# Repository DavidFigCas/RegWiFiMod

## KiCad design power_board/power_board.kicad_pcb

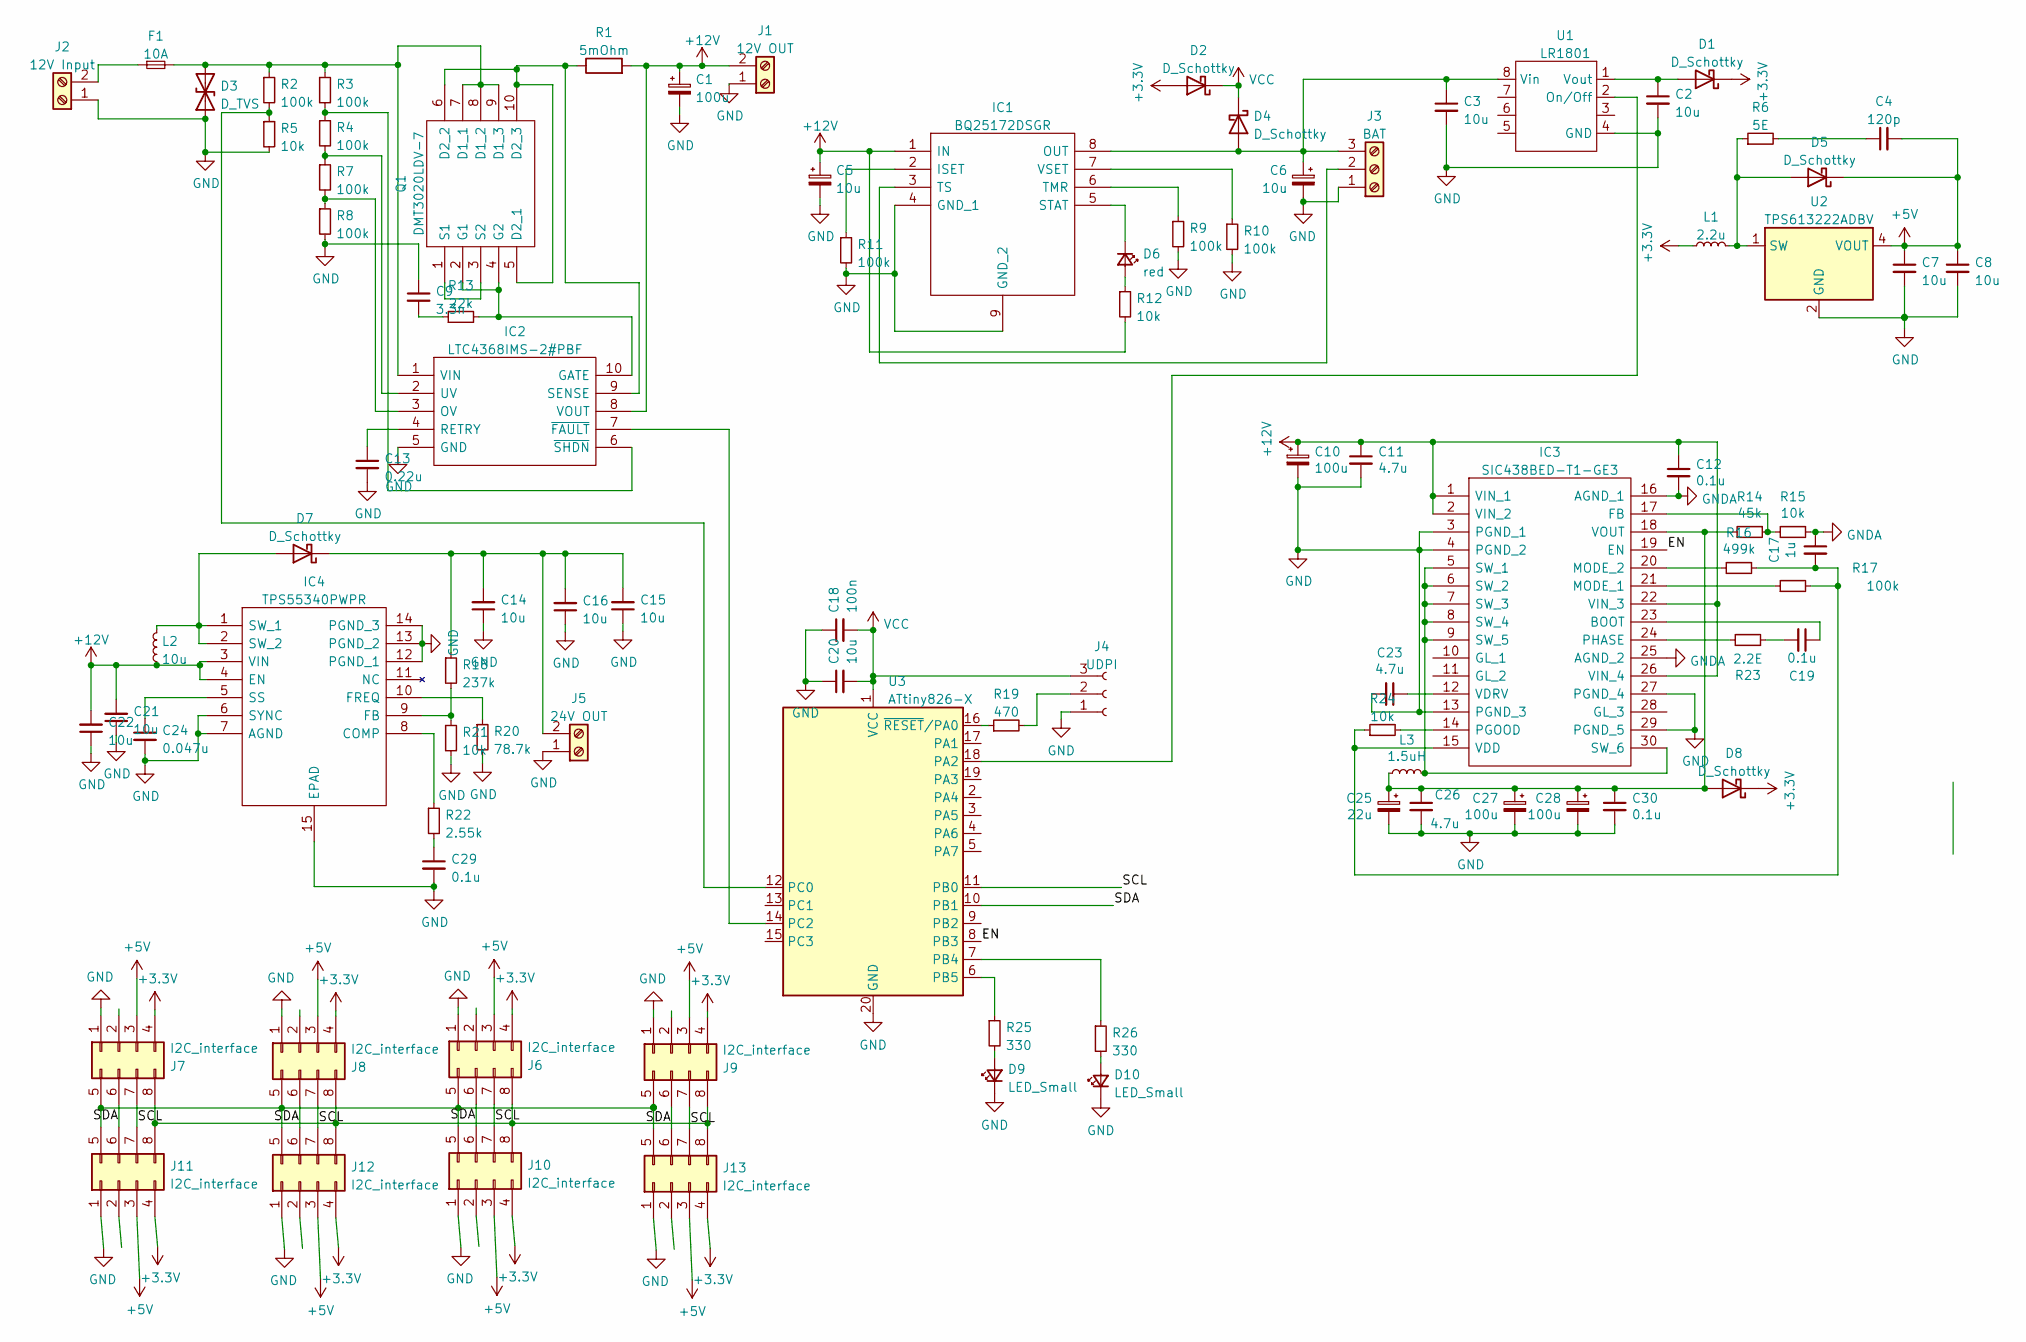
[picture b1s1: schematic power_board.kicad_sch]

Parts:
C1: 100u; CP_Elec_6.3x7.7
C2, C3, C5, C6, C7, C8, C14, C15, C16, C20, C21, C22: 10u; C_0805_2012Metric_Pad1.18x1.45mm_HandSolder
C4: 120p; C_0805_2012Metric_Pad1.18x1.45mm_HandSolder
C9: 3.3n; C_0805_2012Metric_Pad1.18x1.45mm_HandSolder
C10: 100u; CP_Elec_8x10.5
C11, C23, C26: 4.7u; C_0805_2012Metric_Pad1.18x1.45mm_HandSolder
C12, C19, C29, C30: 0.1u; C_0805_2012Metric_Pad1.18x1.45mm_HandSolder
C13: 0.22u; C_0805_2012Metric_Pad1.18x1.45mm_HandSolder
C17: 1u; C_0805_2012Metric_Pad1.18x1.45mm_HandSolder
C18: 100n; C_0805_2012Metric_Pad1.18x1.45mm_HandSolder
C24: 0.047u; C_0805_2012Metric_Pad1.18x1.45mm_HandSolder
C25: 22u; CP_Elec_6.3x3.9
C27, C28: 100u; CP_Elec_6.3x3.9
D1, D2, D4, D5, D8: D_Schottky; D_SOD-128
D3: D_TVS; D_SMA-SMB_Universal_Handsoldering
D6: red; LED_0603_1608Metric_Pad1.05x0.95mm_HandSolder
D7: D_Schottky; TO-277A
D9, D10: LED_Small; LED_0603_1608Metric_Pad1.05x0.95mm_HandSolder
F1: 10A; FUSE_HOLDER
IC1: BQ25172DSGR; SON50P200X200X80-9N; Manufacturer_Part_Number BQ25172DSGR; Mouser Part Number 595-BQ25172DSGR
IC2: LTC4368IMS-2#PBF; SOP50P490X110-10N; Manufacturer_Part_Number LTC4368IMS-2#PBF; Mouser Part Number 584-LTC4368IMS2PBF
IC3: SIC438BED-T1-GE3; SIC438BEDT1GE3; Manufacturer_Part_Number SIC438BED-T1-GE3; Mouser Part Number 78-SIC438BED-T1-GE3
IC4: TPS55340PWPR; SOP65P640X120-15N; Manufacturer_Part_Number TPS55340PWPR; Mouser Part Number 595-TPS55340PWPR
J1: 12V OUT; TerminalBlock_bornier-2_P5.08mm
J2: 12V Input; TerminalBlock_Dinkle_DT-55-B01X-02_P10.00mm
J3: BAT; TerminalBlock_bornier-3_P5.08mm
J4: UDPI; PinHeader_1x03_P2.54mm_Vertical
J5: 24V OUT; TerminalBlock_bornier-2_P5.08mm
J6, J7, J8, J9, J10, J11, J12, J13: I2C_interface; card_connector
L1: 2.2u; L_Bourns_SRN6045TA
L2: 10u; L_Sunlord_MWSA1003S
L3: 1.5uH; L_Sunlord_MWSA1003S
Q1: DMT3020LDV-7; DMT3020LDV7; Manufacturer_Part_Number DMT3020LDV-7; Mouser Part Number 621-DMT3020LDV-7
R1: 5mOhm; R_2512_6332Metric_Pad1.40x3.35mm_HandSolder
R2, R3, R4, R7, R8, R9, R10, R11, R17: 100k; R_0805_2012Metric_Pad1.20x1.40mm_HandSolder
R5, R12, R15, R21, R24: 10k; R_0805_2012Metric_Pad1.20x1.40mm_HandSolder
R6: 5E; R_0805_2012Metric_Pad1.20x1.40mm_HandSolder
R13: 22k; R_0805_2012Metric_Pad1.20x1.40mm_HandSolder
R14: 45k; R_0805_2012Metric_Pad1.20x1.40mm_HandSolder
R16: 499k; R_0805_2012Metric_Pad1.20x1.40mm_HandSolder
R18: 237k; R_0805_2012Metric_Pad1.20x1.40mm_HandSolder
R19: 470; R_0805_2012Metric_Pad1.20x1.40mm_HandSolder
R20: 78.7k; R_0805_2012Metric_Pad1.20x1.40mm_HandSolder
R22: 2.55k; R_0805_2012Metric_Pad1.20x1.40mm_HandSolder
R23: 2.2E; R_0805_2012Metric_Pad1.20x1.40mm_HandSolder
R25, R26: 330; R_0805_2012Metric_Pad1.20x1.40mm_HandSolder
U1: LR1801; HSOP-8-1EP_3.9x4.9mm_P1.27mm_EP2.41x3.1mm_ThermalVias
U2: TPS613222ADBV; SOT-23-5
U3: ATtiny826-X; SSOP-20_5.3x7.2mm_P0.65mm

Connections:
+3V3: D1.1 (K), D2.2 (A), D8.1 (K), J6.4, J7.4, J8.4, J9.4, J10.4, J11.4, J12.4, J13.4, L1.1
+5V: C4.2, C7.1, C8.1, D5.1 (K), J6.3, J7.3, J8.3, J9.3, J10.3, J11.3, J12.3, J13.3, U2.4 (VOUT)
+12V: C1.1, C5.1, C10.1, C11.1, C12.1, C21.2, C22.2, IC1.1 (IN), IC2.8 (VOUT), IC3.1 (VIN_1), IC3.2 (VIN_2), IC3.22 (VIN_3), IC3.26 (VIN_4), IC4.3 (VIN), IC4.4 (EN), J1.2, L2.1, R1.2, R12.2
/EN: IC3.19 (EN), U3.8 (PB3)
/SCL: J6.7, J7.7, J8.7, J9.7, J10.7, J11.7, J12.7, J13.7, U3.11 (PB0)
GND: C1.2, C2.2, C3.2, C5.2, C6.2, C7.2, C8.2, C9.1, C10.2, C11.2, C13.2, C14.1, C15.1, C16.1, C18.1, C20.1, C21.1, C22.1, C23.2, C24.2, C25.2, C26.2, C27.2, C28.2, C29.2, C30.2, D3.1 (A1), D9.1 (K), D10.1 (K), IC1.4 (GND_1), IC1.9 (GND_2), IC2.5 (GND), IC3.3 (PGND_1), IC3.4 (PGND_2), IC3.13 (PGND_3), IC3.27 (PGND_4), IC3.29 (PGND_5), IC4.6 (SYNC), IC4.7 (AGND), IC4.12 (PGND_1), IC4.13 (PGND_2), IC4.14 (PGND_3), IC4.15 (EPAD), J1.1, J2.1, J3.1, J4.1, J5.1, J6.1, J7.1, J8.1, J9.1, J10.1, J11.1, J12.1, J13.1, R5.2, R8.2, R9.2, R10.2, R11.2, R20.2, R21.2, U1.4 (GND), U2.2 (GND), U3.20 (GND)
GNDA: C12.2, C17.1, IC3.16 (AGND_1), IC3.25 (AGND_2), R15.1
unnamed: C2.1, D1.2 (A), U1.1 (Vout)
unnamed: C3.1, C6.1, D4.2 (A), IC1.8 (OUT), J3.3, U1.8 (Vin)
unnamed: C4.1, R6.2
unnamed: C9.2, R13.1
unnamed: C13.1, IC2.4 (RETRY)
unnamed: C14.2, C15.2, C16.2, D7.1 (K), J5.2, R18.1
unnamed: C17.2, IC3.15 (VDD), R16.1, R17.2, R24.1
unnamed: C19.1, IC3.23 (BOOT)
unnamed: C19.2, R23.1
unnamed: C23.1, IC3.12 (VDRV)
unnamed: C24.1, IC4.5 (SS)
unnamed: C25.1, C26.1, C27.1, C28.1, C30.1, D8.2 (A), IC3.18 (VOUT), L3.1, R14.2
unnamed: C29.1, R22.2
unnamed: D3.2 (A2), F1.2, IC2.1 (VIN), Q1.7 (D1_1), Q1.8 (D1_2), Q1.9 (D1_3), R2.1, R3.1
unnamed: D5.2 (A), L1.2, R6.1, U2.1 (SW)
unnamed: D6.1 (K), IC1.5 (STAT)
unnamed: D6.2 (A), R12.1
unnamed: D7.2 (A), IC4.1 (SW_1), IC4.2 (SW_2), L2.2
unnamed: D9.2 (A), R25.2
unnamed: D10.2 (A), R26.2
unnamed: F1.1, J2.2
unnamed: IC1.2 (ISET), R11.1
unnamed: IC1.3 (TS), J3.2
unnamed: IC1.6 (TMR), R9.1
unnamed: IC1.7 (VSET), R10.1
unnamed: IC2.2 (UV), R4.2, R7.1
unnamed: IC2.3 (OV), R7.2, R8.1
unnamed: IC2.6 (~SHDN), R3.2, R4.1
unnamed: IC2.7 (~FAULT), U3.14 (PC2)
unnamed: IC2.9 (SENSE), Q1.5 (D2_1), Q1.6 (D2_2), Q1.10 (D2_3), R1.1
unnamed: IC2.10 (GATE), Q1.2 (G1), Q1.4 (G2), R13.2
unnamed: IC3.14 (PGOOD), R24.2
unnamed: IC3.17 (FB), R14.1, R15.2
unnamed: IC3.20 (MODE_2), R16.2
unnamed: IC3.21 (MODE_1), R17.1
unnamed: IC3.24 (PHASE), R23.2
unnamed: IC3.5 (SW_1), IC3.6 (SW_2), IC3.7 (SW_3), IC3.8 (SW_4), IC3.9 (SW_5), IC3.30 (SW_6), L3.2
unnamed: IC4.8 (COMP), R22.1
unnamed: IC4.9 (FB), R18.2, R21.1
unnamed: IC4.10 (FREQ), R20.1
unnamed: J4.2, R19.2
unnamed: J6.5, J7.5, J8.5, J9.5, J10.5, J11.5, J12.5, J13.5
unnamed: Q1.1 (S1), Q1.3 (S2)
unnamed: R2.2, R5.1, U3.12 (PC0)
unnamed: R19.1, U3.16 (~RESET/PA0)
unnamed: R25.1, U3.6 (PB5)
unnamed: R26.1, U3.7 (PB4)
unnamed: U1.2 (On/Off), U3.18 (PA2)
VCC: C18.2, C20.2, D2.1 (K), D4.1 (K), J4.3, U3.1 (VCC)

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
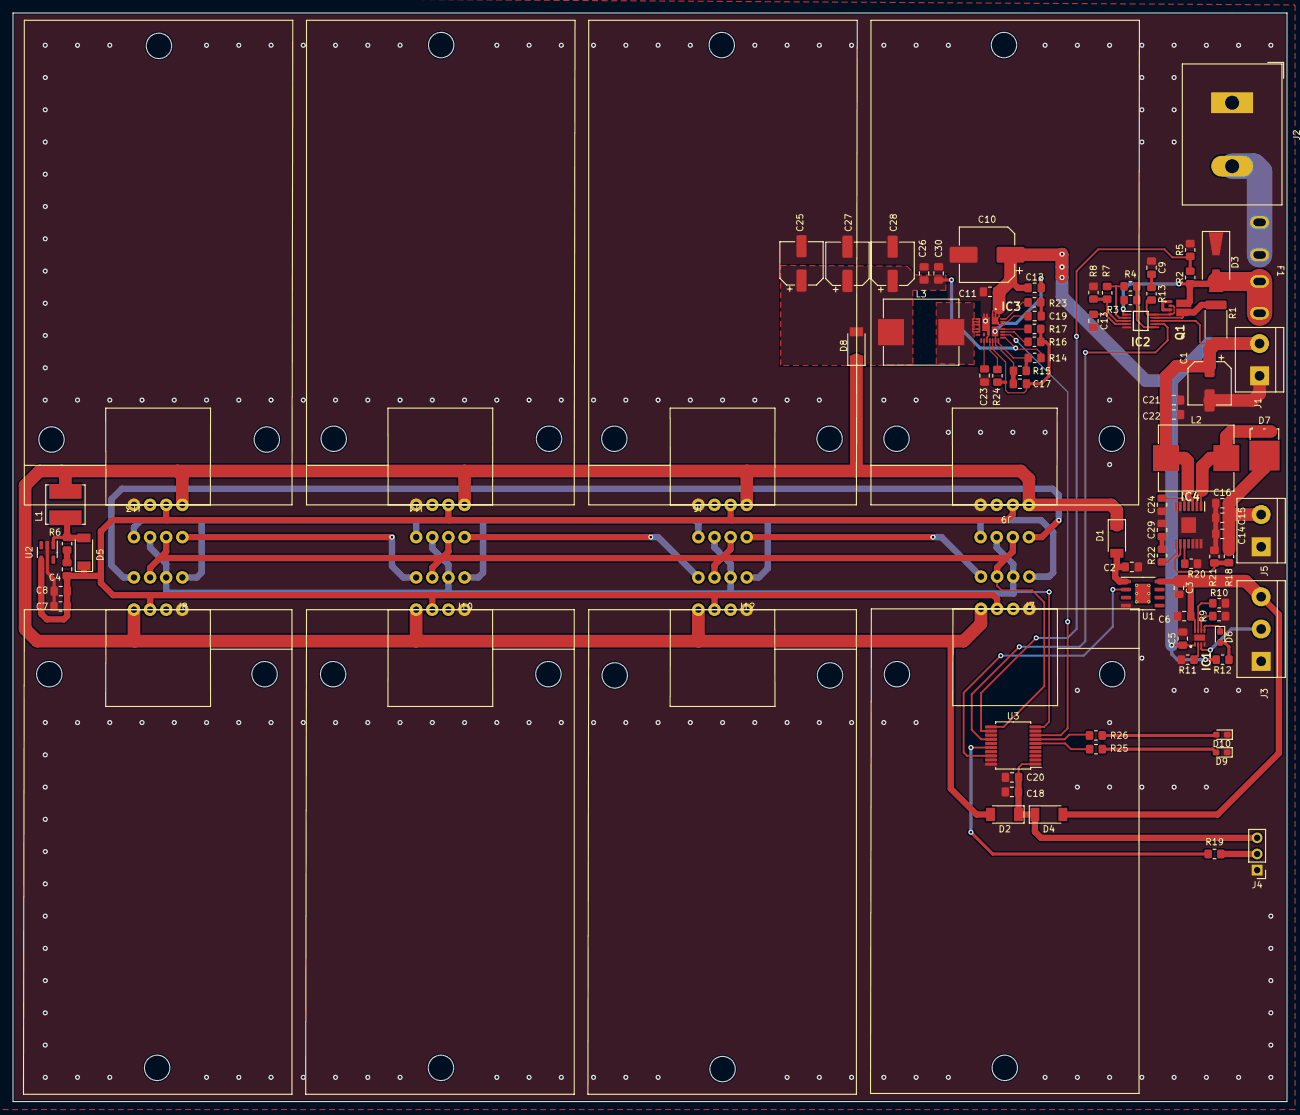
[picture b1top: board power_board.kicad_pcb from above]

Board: 2 copper layers, 200.7 x 171.5 mm, 91 parts (0 on the bottom side), 58 nets.

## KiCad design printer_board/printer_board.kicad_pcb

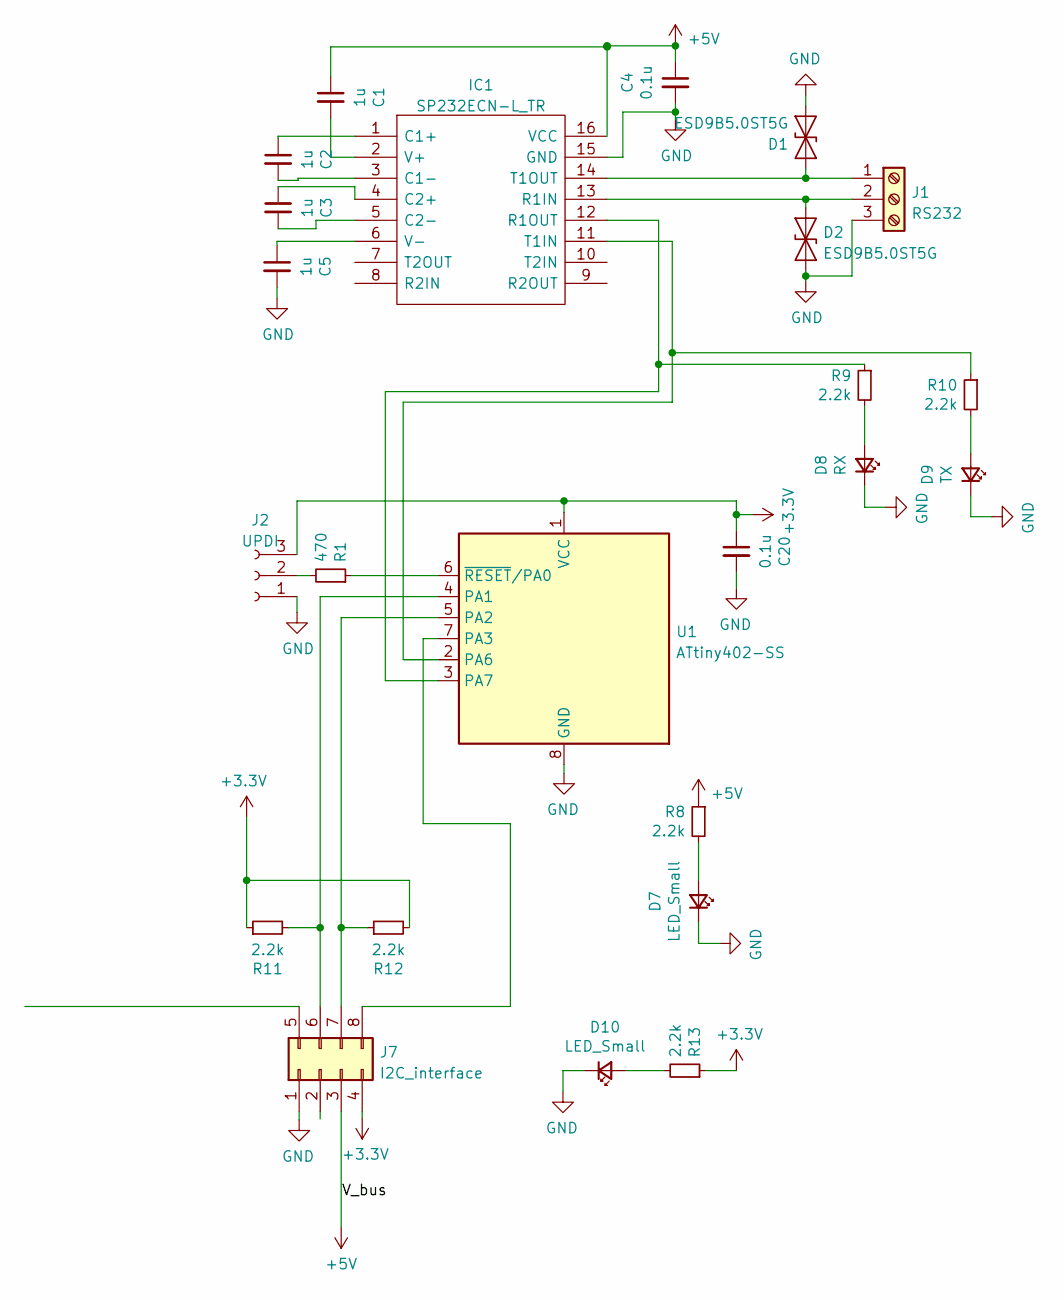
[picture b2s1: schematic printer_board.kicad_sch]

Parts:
C1, C2, C3, C5: 1u; C_0805_2012Metric_Pad1.18x1.45mm_HandSolder
C4, C20: 0.1u; C_0805_2012Metric_Pad1.18x1.45mm_HandSolder
D1, D2: ESD9B5.0ST5G; D_0603_1608Metric_Pad1.05x0.95mm_HandSolder
D7, D10: LED_Small; LED_0603_1608Metric_Pad1.05x0.95mm_HandSolder
D8: RX; LED_0603_1608Metric_Pad1.05x0.95mm_HandSolder
D9: TX; LED_0603_1608Metric_Pad1.05x0.95mm_HandSolder
IC1: SP232ECN-L_TR; SOIC127P600X175-16N; Manufacturer_Part_Number SP232ECN-L/TR; Mouser Part Number 701-SP232ECN-L/TR
J1: RS232; TerminalBlock_4Ucon_1x03_P3.50mm_Horizontal
J2: UPDI; PinHeader_1x03_P2.54mm_Vertical
J7: I2C_interface; connector_pcb
R1: 470; R_0805_2012Metric_Pad1.20x1.40mm_HandSolder
R8, R9, R10, R11, R12, R13: 2.2k; R_0805_2012Metric_Pad1.20x1.40mm_HandSolder
U1: ATtiny402-SS; SOIC-8_3.9x4.9mm_P1.27mm

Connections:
+3V3: C20.1, J2.3, J7.4, R11.1, R12.2, R13.1, U1.1 (VCC)
+5V: C1.1, C4.1, IC1.16 (VCC), J7.3, R8.1
GND: C4.2, C5.2, C20.2, D1.1 (A1), D2.1 (A1), D7.1 (K), D8.1 (K), D9.1 (K), D10.1 (K), IC1.15 (GND), J1.3, J2.1, J7.1, U1.8 (GND)
unnamed: C1.2, IC1.2 (V+)
unnamed: C2.1, IC1.1 (C1+)
unnamed: C2.2, IC1.3 (C1-)
unnamed: C3.1, IC1.4 (C2+)
unnamed: C3.2, IC1.5 (C2-)
unnamed: C5.1, IC1.6 (V-)
unnamed: D1.2 (A2), IC1.14 (T1OUT), J1.1
unnamed: D2.2 (A2), IC1.13 (R1IN), J1.2
unnamed: D7.2 (A), R8.2
unnamed: D8.2 (A), R9.2
unnamed: D9.2 (A), R10.2
unnamed: D10.2 (A), R13.2
unnamed: J2.2, R1.2
unnamed: J7.6, R11.2, U1.4 (PA1)
unnamed: J7.7, R12.1, U1.5 (PA2)
unnamed: J7.8, U1.7 (PA3)
unnamed: R1.1, U1.6 (~RESET/PA0)
unnamed: IC1.12 (R1OUT), R9.1, U1.3 (PA7)
unnamed: IC1.11 (T1IN), R10.1, U1.2 (PA6)

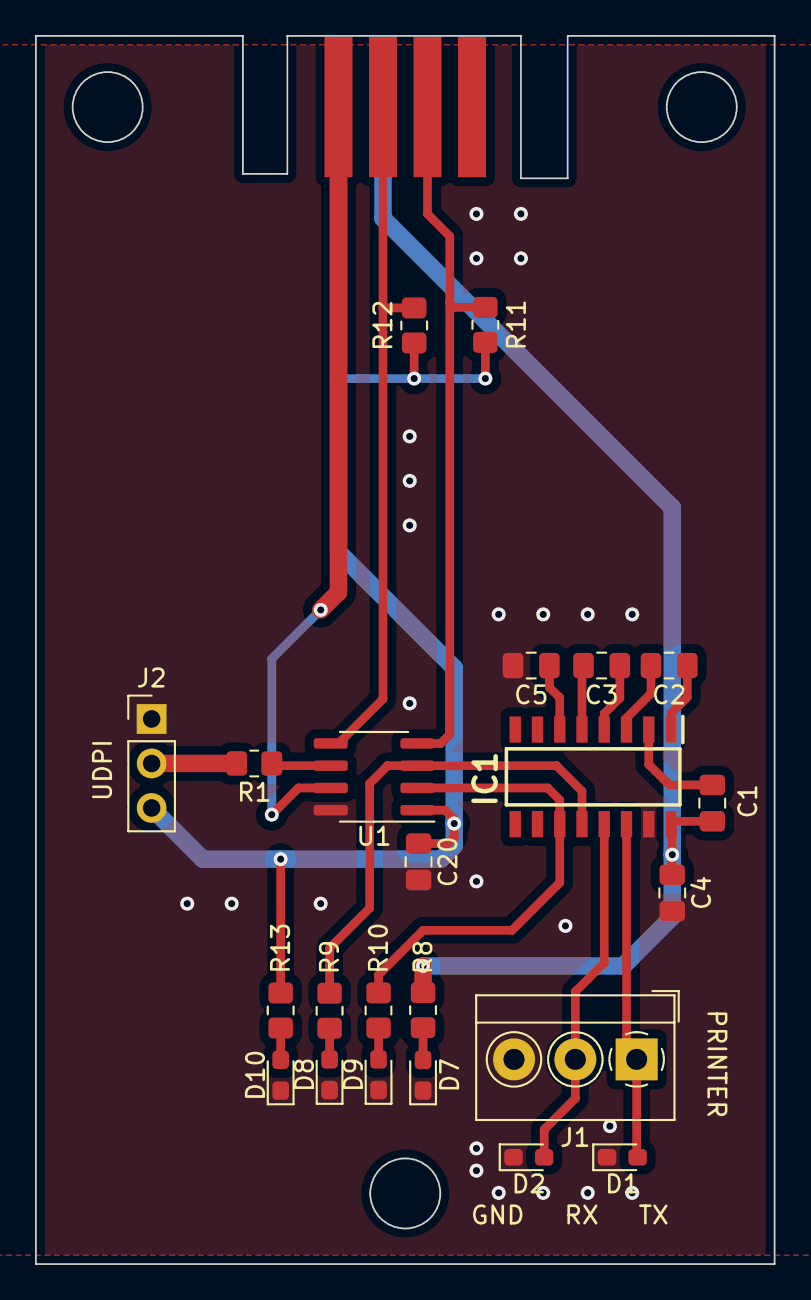
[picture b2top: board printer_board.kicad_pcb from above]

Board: 2 copper layers, 42.2 x 70.1 mm, 24 parts (1 on the bottom side), 22 nets.

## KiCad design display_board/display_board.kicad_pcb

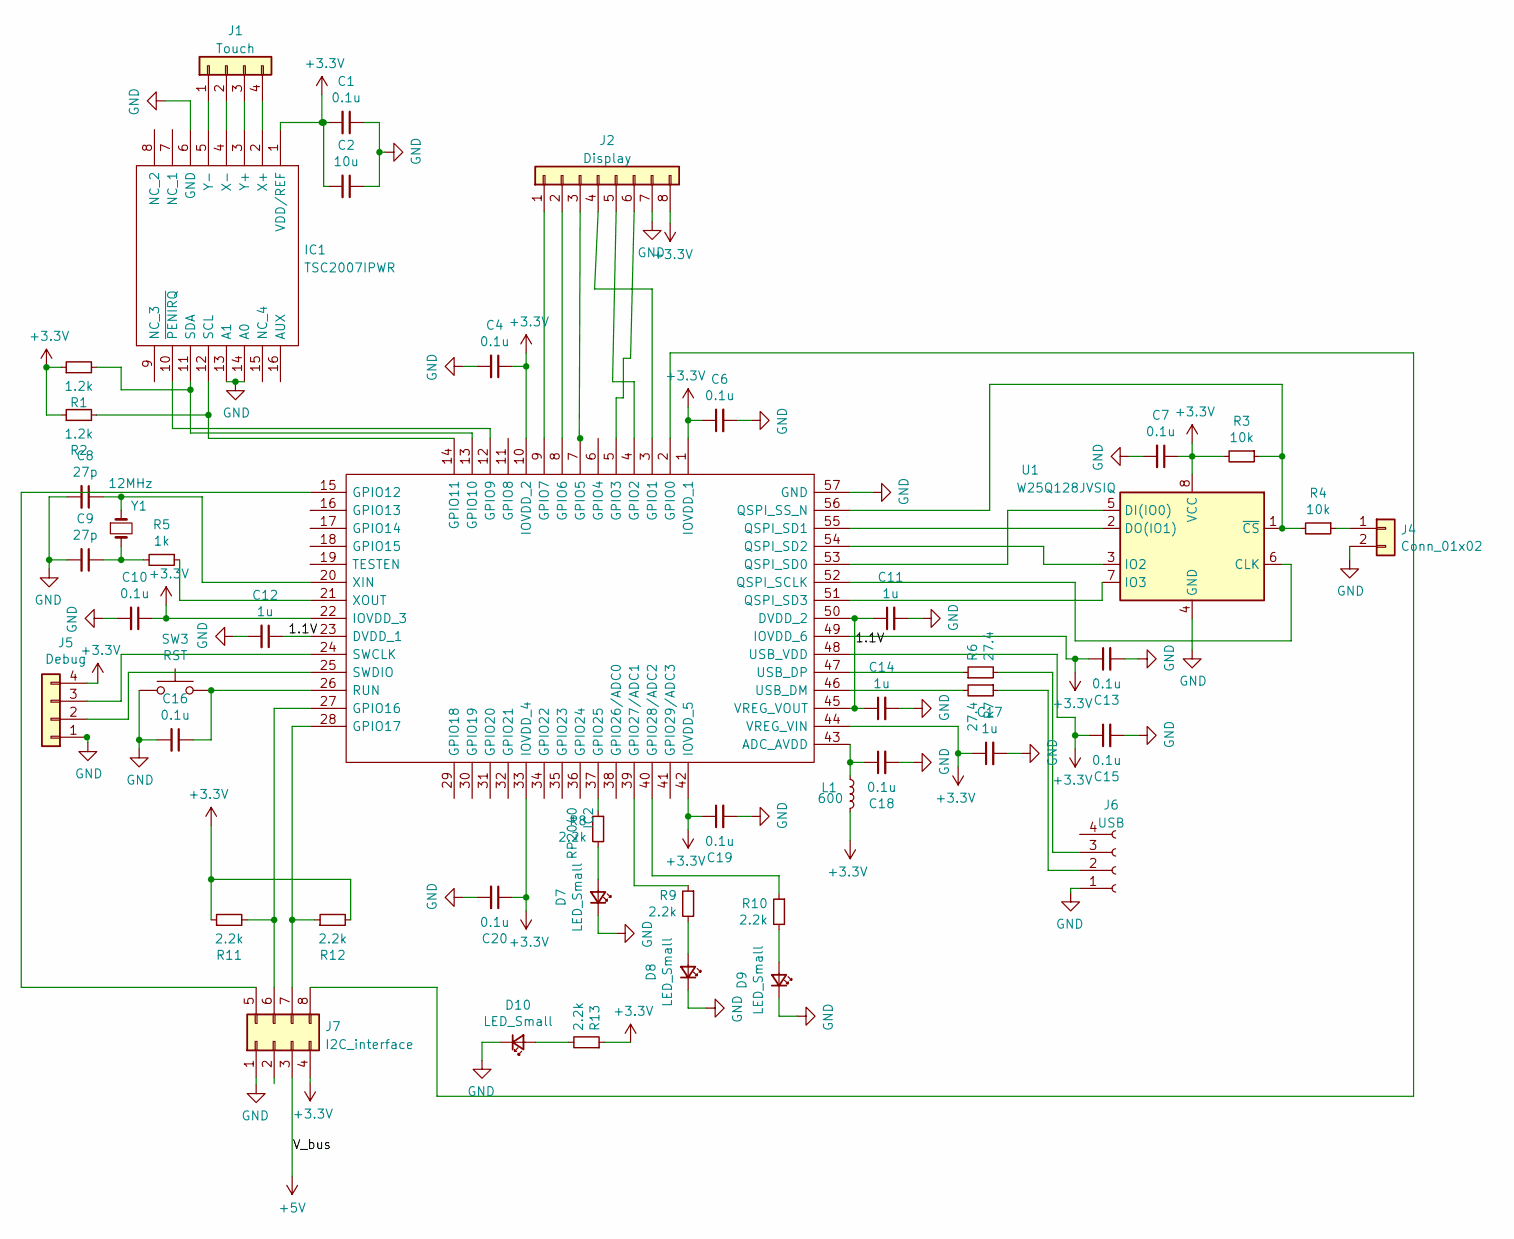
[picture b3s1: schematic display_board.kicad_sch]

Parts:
C1, C4, C6, C7, C10, C13, C15, C16, C18, C19, C20: 0.1u; C_0805_2012Metric_Pad1.18x1.45mm_HandSolder
C2: 10u; C_0805_2012Metric_Pad1.18x1.45mm_HandSolder
C8, C9: 27p; C_0805_2012Metric_Pad1.18x1.45mm_HandSolder
C11, C12, C14, C17: 1u; C_0805_2012Metric_Pad1.18x1.45mm_HandSolder
D7, D8, D9, D10: LED_Small; LED_0603_1608Metric_Pad1.05x0.95mm_HandSolder
IC1: TSC2007IPWR; SOP65P640X120-16N; Manufacturer_Part_Number TSC2007IPWR; Mouser Part Number 595-TSC2007IPWR
IC2: RP2040; QFN40P700X700X90-57N-D; Manufacturer_Part_Number RP2040
J1: Touch; touch
J2: Display; PinHeader_1x08_P2.00mm_Horizontal
J4: Conn_01x02; SW_SPST_B3S-1000
J5: Debug; PinSocket_1x04_P2.54mm_Vertical
J6: USB; PinHeader_1x04_P2.54mm_Vertical
J7: I2C_interface; connector_pcb
L1: 600; L_1206_3216Metric_Pad1.22x1.90mm_HandSolder
R1, R2: 1.2k; R_0805_2012Metric_Pad1.20x1.40mm_HandSolder
R3, R4: 10k; R_0805_2012Metric_Pad1.20x1.40mm_HandSolder
R5: 1k; R_0805_2012Metric_Pad1.20x1.40mm_HandSolder
R6, R7: 27.4; R_0805_2012Metric_Pad1.20x1.40mm_HandSolder
R8, R9, R10, R11, R12, R13: 2.2k; R_0805_2012Metric_Pad1.20x1.40mm_HandSolder
SW3: RST; SW_SPST_B3S-1000
U1: W25Q128JVSIQ; SOP-8_5.28x5.23mm_P1.27mm
Y1: 12MHz; Crystal_SMD_HC49-SD

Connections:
+3V3: C1.2, C2.2, C4.1, C6.1, C7.1, C10.1, C13.1, C15.1, C17.1, C19.1, C20.1, IC1.1 (VDD/REF), IC2.1 (IOVDD_1), IC2.10 (IOVDD_2), IC2.22 (IOVDD_3), IC2.33 (IOVDD_4), IC2.42 (IOVDD_5), IC2.44 (VREG_VIN), IC2.48 (USB_VDD), IC2.49 (IOVDD_6), J2.8, J5.4, J7.4, L1.2, R1.1, R2.1, R3.2, R11.1, R12.2, R13.1, U1.8 (VCC)
+5V: J7.3
/1.1V: C11.1, C12.1, C14.1, IC2.23 (DVDD_1), IC2.45 (VREG_VOUT), IC2.50 (DVDD_2)
GND: C1.1, C2.1, C4.2, C6.2, C7.2, C8.2, C9.2, C10.2, C11.2, C12.2, C13.2, C14.2, C15.2, C16.2, C17.2, C18.2, C19.2, C20.2, D7.1 (K), D8.1 (K), D9.1 (K), D10.1 (K), IC1.6 (GND), IC1.13 (A1), IC1.14 (A0), IC2.57 (GND), J2.7, J4.2, J5.1, J6.1, J7.1, SW3.1, U1.4 (GND)
unnamed: C8.1, IC2.20 (XIN), Y1.1
unnamed: C9.1, R5.2, Y1.2
unnamed: C16.1, IC2.26 (RUN), SW3.2
unnamed: C18.1, IC2.43 (ADC_AVDD), L1.1
unnamed: D7.2 (A), R8.2
unnamed: D8.2 (A), R9.2
unnamed: D9.2 (A), R10.2
unnamed: D10.2 (A), R13.2
unnamed: IC1.2 (X+), J1.4
unnamed: IC1.3 (Y+), J1.3
unnamed: IC1.4 (X-), J1.2
unnamed: IC1.5 (Y-), J1.1
unnamed: IC2.2 (GPIO0), J7.8
unnamed: IC2.3 (GPIO1), J2.4
unnamed: IC2.4 (GPIO2), J2.5
unnamed: IC2.5 (GPIO3), J2.6
unnamed: IC2.7 (GPIO5), J2.3
unnamed: IC2.8 (GPIO6), J2.2
unnamed: IC2.9 (GPIO7), J2.1
unnamed: IC1.10 (~PENIRQ), IC2.12 (GPIO9)
unnamed: IC1.11 (SDA), IC2.13 (GPIO10), R1.2
unnamed: IC1.12 (SCL), IC2.14 (GPIO11), R2.2
unnamed: IC2.15 (GPIO12), J7.5
unnamed: IC2.21 (XOUT), R5.1
unnamed: IC2.24 (SWCLK), J5.3
unnamed: IC2.25 (SWDIO), J5.2
unnamed: IC2.27 (GPIO16), J7.6, R11.2
unnamed: IC2.28 (GPIO17), J7.7, R12.1
unnamed: IC2.37 (GPIO25), R8.1
unnamed: IC2.39 (GPIO27/ADC1), R9.1
unnamed: IC2.40 (GPIO28/ADC2), R10.1
unnamed: IC2.46 (USB_DM), R7.2
unnamed: IC2.47 (USB_DP), R6.1
unnamed: IC2.51 (QSPI_SD3), U1.7 (IO3)
unnamed: IC2.52 (QSPI_SCLK), U1.6 (CLK)
unnamed: IC2.53 (QSPI_SD0), U1.5 (DI(IO0))
unnamed: IC2.54 (QSPI_SD2), U1.3 (IO2)
unnamed: IC2.55 (QSPI_SD1), U1.2 (DO(IO1))
unnamed: IC2.56 (QSPI_SS_N), R3.1, R4.2, U1.1 (~CS)
unnamed: J4.1, R4.1
unnamed: J6.2, R7.1
unnamed: J6.3, R6.2

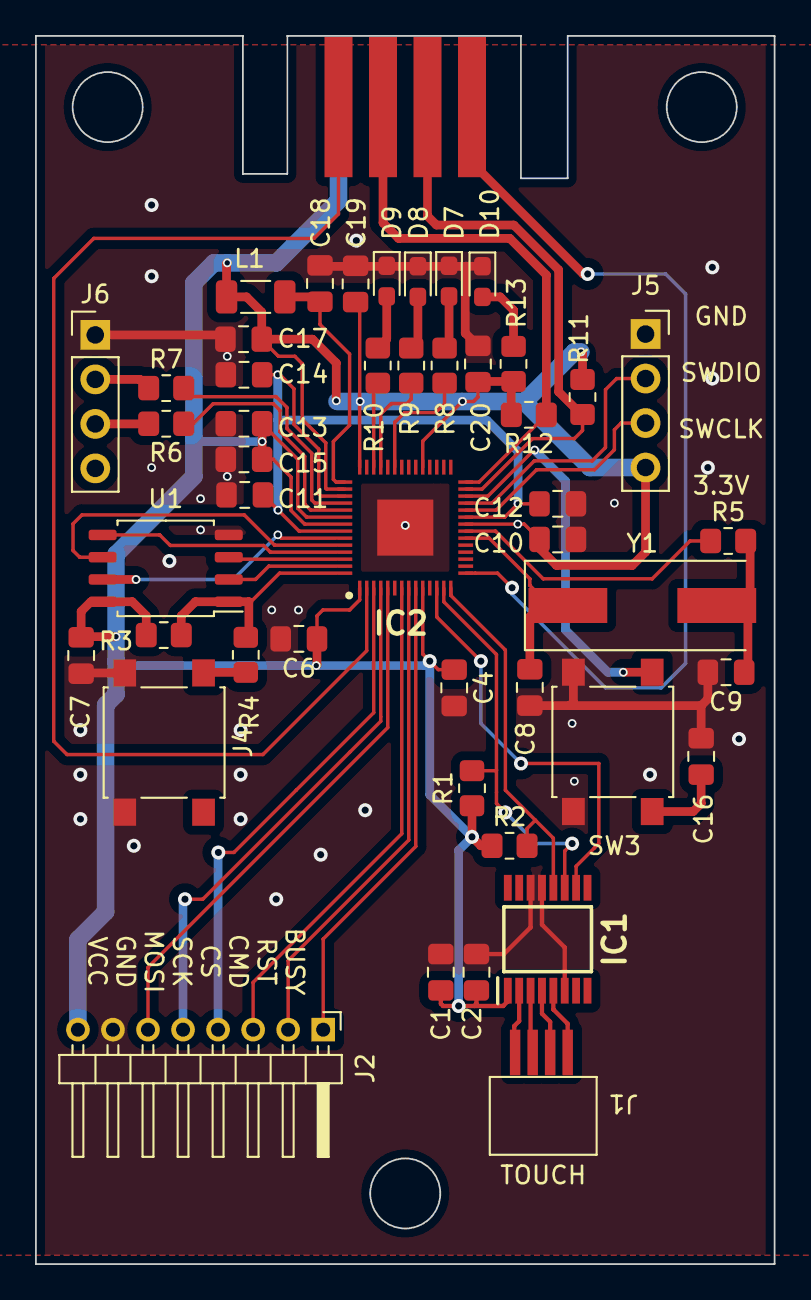
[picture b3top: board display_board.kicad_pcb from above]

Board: 2 copper layers, 42.2 x 70.1 mm, 47 parts (1 on the bottom side), 45 nets.

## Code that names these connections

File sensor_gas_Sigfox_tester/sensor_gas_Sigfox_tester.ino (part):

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


#define RESET_RADIO   PIN_PA6

#define INICIO    0
#define PROCESO   1
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// ----------------------------------------------------------- initSensor
void initSensor()
{
  pinMode(PIN_PB1, INPUT_PULLUP);
  pinMode(PIN_PB0, INPUT_PULLUP);
  Wire.begin();
  //delay(50);

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
  //Serial1.end();
  //Wire.end();
  //pinMode(PIN_PA0, INPUT);
  //pinMode(PIN_PA1, INPUT);
  //pinMode(PIN_PA2, INPUT);
  pinMode(PIN_PA3, INPUT);
  pinMode(PIN_PA4, INPUT);
  pinMode(PIN_PA5, INPUT);
  pinMode(PIN_PA6, INPUT);
  pinMode(PIN_PA7, INPUT);


  pinMode(PIN_PB0, INPUT);
  pinMode(PIN_PB1, INPUT);
  pinMode(PIN_PB2, INPUT);
  pinMode(PIN_PB3, INPUT);
  pinMode(PIN_PB4, INPUT);
  pinMode(PIN_PB5, INPUT);

  pinMode(PIN_PC0, INPUT);
  pinMode(PIN_PC1, INPUT);
  pinMode(PIN_PC2, INPUT);
  pinMode(PIN_PC3, INPUT);

  //digitalWrite(PIN_PA0, HIGH);
  //digitalWrite(PIN_PA1, HIGH);
  //digitalWrite(PIN_PA2, HIGH);
  digitalWrite(PIN_PA3, HIGH);
  digitalWrite(PIN_PA4, HIGH);
  digitalWrite(PIN_PA5, HIGH);
  digitalWrite(PIN_PA6, LOW);
  digitalWrite(PIN_PA7, HIGH);

  digitalWrite(PIN_PB0, HIGH);
  digitalWrite(PIN_PB1, HIGH);
  digitalWrite(PIN_PB2, HIGH);
  digitalWrite(PIN_PB3, HIGH);
  digitalWrite(PIN_PB4, HIGH);
  digitalWrite(PIN_PB5, HIGH);

  digitalWrite(PIN_PC0, HIGH);
  digitalWrite(PIN_PC1, HIGH);
  digitalWrite(PIN_PC2, HIGH);
  digitalWrite(PIN_PC3, HIGH);
  //Serial1.end();

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
  //USART0.CTRLB |= (USART_RXEN_bm | USART_TXEN_bm); // Activa transmisor y receptor
  //Serial1.begin(9600);
  //pinMode(PIN_PA0, INPUT_PULLUP);

  //sleep_disable(); // Deshabilitar modo de sueño después de despertar
  //power_all_enable();
  //ADC0.CTRLA |= ADC_ENABLE_bm;
  //pinMode(PIN_PA0, INPUT_PULLUP);

  //TCA0.SINGLE.CTRLA |= TCA_SINGLE_ENABLE_bm; // Habilitar TCA0
  //TCB0.CTRLA |= TCB_ENABLE_bm; // Habilitar TCB0
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
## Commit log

2023-10-05 init
2023-10-05 init 2
2023-10-05 other
2023-10-05 adapt
2023-10-07 testing but not work
2023-10-08 add and list ready, i2c not working yet
2023-10-08 medio
2023-10-08 cambios es tamaño de json documents genera errores, funcional ahora
2023-10-08 StaticJson
    Entiendo que Static se mantiene y dynamic se fragmenta
2023-10-09 Error resuelto de MQTT enable y Static en todos
2023-10-10 i2c slave ok and clock
2023-10-11 Lee i2c una de dos
2023-10-11 Funciona la busqueda en el array, i2c funciona 1 de 2
2023-10-12 listo en la busqueda del id del cliente y la puesta en los registros
2023-10-12 star gpsd test serial
2023-10-13 gps listo, log casi listo
2023-10-13 gps object statatus
2023-10-13 El metodo para extraer ssid del obj se cambio, fallaba
2023-10-13 working togeter master and slave
2023-10-13 ajustes en el i2c_slave_handler
2023-10-14 trabajando en el log
2023-10-17 factro client price register ready
2023-10-17 testing
2023-10-18 not ready
2023-10-26 try to place toggeter
2023-10-27 esp32 ready master
2023-10-27 esp compiling
2023-10-28 2 cores working
2023-10-28 aqui empece a trabajar en varias maquinas
2023-10-28 PRUEBA
2023-10-28 se regresa la dirección
2023-10-29 prueba de lectura pines
2023-10-29 josn obj runing
2023-10-29 Display STATE Icosn works
2023-10-29 envio de litros, display ready
2023-10-29 encoder pulsos works
2023-10-29 Master printer actualizado
2023-10-30 encoder ready
2023-10-30 master wip
2023-10-30 not ready, delay at star for prevent
2023-10-30 moviendo delay, a veces el encoder no responde
2023-10-31 Trabajando en la estabilidad, el display toma delay al inicio o se traba
2023-10-31 depurando el encoder
    se quito old_value_m y current_value
2023-10-31 master printer from Roman
2023-10-31 wip forward
2023-10-31 se encima la impresora, pero el init hace errores
2023-10-31 display module works and encoder and master
2023-10-31 imprime
2023-10-31 litros se esta llendo a cero en algun momento
2023-10-31 master_module
2023-10-31 master_esp32 wip
2023-10-31 Se repite la impresion infinitamente
2023-10-31 firebase wip
2023-10-31 no recive por mqtt, el log no se guarda, no mantene folio
2023-10-31 encoder_fix uint for direction
2023-10-31 display_module fix final numbers
    i2c Interrupt update jsonobj
2023-10-31 se ajustó el tamaño de los buffers en mqtt para evitar sobreflujo
2023-10-31 no firebase
2023-10-31 veracruz + firebase
2023-11-01 testing space
2023-11-01 unix time ready on screen
2023-11-01 wip printing logs
2023-11-01 encoder con define delta y master con print log
2023-11-01 guarda el log inmediatamente
2023-11-01 binario
2023-11-01 update litros on display
2023-11-01 ajustes de capacidades de memoria y piopin para imprimir
2023-11-01 binario
    binario, falta agregar que con ese boton pueda tambien borrar todo el long si lo dejan precionado
2023-11-01 binario 1.0.6
2023-11-01 Binario 1.0.7
    Boton para imprimir la lista y borrar si se deja presionado 5 seg
2023-11-01 cambio de orden en la inicializacion, solo estetica
2023-11-02 Revert "cambio de orden en la inicializacion, solo estetica"
    This reverts commit 5f3d23ffbca41bc7bc73b47bc2faab11285c508d.
2023-11-07 test report
2023-11-07 correcion en el folio y la logica de los logs
2023-11-07 encoder log ready, not lust
2023-11-07 CAMBIANDO ESTILO
2023-11-07 add flag ready to print
2023-11-08 añadiendo display oled
    falta agregar comando mqtt para eliminar log por dia
2023-11-08 funciona con la oled
2023-11-08 wip, la impresion es inestable
2023-11-08 wip, not working
2023-11-08 la impresion al inicio mete el error
2023-11-09 impresion de test y tiempo de espera eliminado
    meten error en el log
2023-11-09 precio y puslsos por litros desde mqtt
2023-11-09 binario dev
2023-11-09 ver 1.0.8 dev y binario
2023-11-09 wip on report
2023-11-09 reporte en prueba
2023-11-09 testing report, force uint32_t
2023-11-13 sensor tele
2023-11-13 tiempos ready
2023-11-14 json wip
    not ready, adding json status to mqtt, funciona solo sas primeras veces
2023-11-14 testing display, se elimino una coma extra con errores
2023-11-14 status_doc and gps wip
2023-11-14 status doc ready
2023-11-14 funciona el status_doc y el update firm
    recibe el comando de update y se conecta firebase
2023-11-14 status_doc ready
2023-11-15 agregando la lcd i2c, no estable
2023-11-15 se guarda cualquier objeto que llegue por config
    falta usar el argumento de usuario y contra en mqtt
2023-11-15 probando mqtt new obj config
    falla, se agrega pretende agregar reinicio de fabrica
2023-11-16 gps manda empty, agrgando wifi manager
2023-11-16 gps init error
    Al iniciar el Serial1 mete error, se esta considerando meter Serial2 por tema de diseño
2023-11-17 wifi manager ready
    mqtt list not ready
2023-11-17 mqtt new list solo acepta pocos argumentos
    falta trabajar en el log de eventos, que guarde por día por ejemplo y se consulte por días
2023-11-17 binarios
    debo agregar otro canal para new_firmware, donde pueda agregar el argumento del archivo a buscar
2023-11-17 corrección en el redonde de litros
    se usa ceil, redonde hacia arriba
2023-11-17 actualiza los parametros correcto
2023-11-17 Active el serial 2 para gps, no se lee aun
2023-11-17 iniciando cambios en la pantalla
2023-11-17 pruebas de display partial update
2023-11-17 trabajando en el display, optimizando
2023-11-18 display wip
2023-11-18 concordancia entre los valores y sus redondeos
2023-11-20 sd test works on wrover
2023-11-20 testing sd card
2023-11-21 sd card log not working, wip
2023-11-21 wip on sd and spiffs log
2023-11-22 wip, hay que dupliar sd card and spiffs
2023-11-22 sd card, read and write, but not load on boot
2023-11-22 load sd ok
2023-11-22 aun es inestable, a veces no guarda
2023-11-23 SD ready
    Cambio de pines de SPI, se usan default, los otros tienen conflicto, ahora se debe probar el maximo tamaño de archivos y el modo de guardarlos
2023-11-23 testing wip
2023-11-23 wip
    correccion para forzado de estado al inicio dekl display
2023-11-23 Error en la funcion de printCheck
    Se desborda el buffer, se cambio de tamaño, aun tiene error en los miles
2023-11-24 almacenamiento estable
    Se almacena el gps en carpeta y archivo con nombre un json cada minuto con un enter, falta enviar y separar por cada enter. se debe cambiar toda la estructura de logs, quitar arrays para evitar carga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
2023-11-24 cuando no encuentra el archivo sobreescribe y borra
    verificar o no borrar el archivo, lo hace cuando ya existe y tien info pero no lo puede abrir
2023-11-24 hay solo una marca de sd que funciona
    deny
2023-11-24 more stable, wip
2023-11-25 wip, no estable al buscar el archivo, lo borra
2023-11-25 funcional y con debug de errores
    el modulo con jumpers genera error, funciona en la espsim700
2023-11-27 sd ready
    json test of files, not good idea, next csv
2023-11-27 sd testing
2023-11-28 csv para gps, json para servicios
2023-11-28 logs reporte correcto
    falta enviar por mqtt
2023-11-28 se envian archivos de la sd
    se usa su nombre y path completo para consultar o imprimir
2023-11-28 dev freRtos
2023-11-28 la tarea de leer los modulos hace reboot
2023-11-28 wip not work
2023-11-29 reset wdt when send mqtt file
2023-11-29 wip total litros
2023-11-30 reporte wip
    trabajar en el numero de folio inicial
2023-11-30 print and folio
2023-12-01 wip works
2023-12-01 sigfox testing
2023-12-02 funcional wip
2023-12-02 funciona cada 15min, led cada min
2023-12-02 funciona, vmin 2.6v all
2023-12-02 radio deep sleep mode and wakeup
2023-12-03 wip listo reset, falta bateria
2023-12-03 15 min si hay sensor 1.5m si no hay
2023-12-04 internal voltage
2023-12-04 funciona, ahora usare stados para no bloquear uart
2023-12-05 wip low power
2023-12-05 low wip
    baja a 157uA, se debe recalcular el relojÇ CCP = 0xD8;
    CLKCTRL.MCLKCTRLA = 1;
    CLKCTRL.OSC32KCTRLA = 1;
2023-12-05 gas sensor
2023-12-08 ready
2023-12-09 envia todos los mensajes, se resetea por pin y por comando
2023-12-18 sigfox
2023-12-27 lcd start
2023-12-29 sleep baja a 25uA
2023-12-29 no LED
2024-01-04 configs
2024-01-04 works sensor x, need two readings
2024-01-04 wip angle
2024-01-04 merge
2024-01-06 angulo en arctan
2024-01-08 Angulo normalizado
2024-01-10 alimentación MLX y pin MS/CS deben ir a VDD
2024-01-11 ready sleep
2024-01-12 1.0.0
2024-01-13 delta change
    1.1.0
2024-01-16 Mejor ajuste en cero, tabla de valores y
    Se agregan 15 grados en la tabla de porcentajes
2024-01-16 1.1.2
    Mejor ajuste en cero, tabla de valores y se agregan 15 grados en la tabla de porcentajes
2024-01-18 Encoder Cuenta Delta y TiempoEspera independiente
    DeltaTime encuentra flow, si flow se detinede le da tiempoespera y si flow en ese tiempo se restablece tiempoespera se reinicia
2024-01-25 display LCD Wip
2024-01-26 error en sobreescritura lcd
2024-01-29 1.1.4
2024-01-29 1.1.4
    raw sensor
2024-02-01 gas reg wip
2024-02-01 1.1.5
    Promedio, normalizado
2024-02-13 sigfox wip, más estable
2024-02-19 main_logic_board + ds1307
    Modulo principal con ds1307 en PCB
2024-02-19 ajustes para PCB
2024-03-01 tester
2024-03-14 imagen tn500
2024-05-16 lcd wip
2024-05-16 display icons wip
2024-05-17 encoder valve wip
2024-05-18 target litros ready wip
2024-05-18 encoder wip
2024-05-18 Display integrando teclado
2024-05-19 encoder total count wip
2024-05-19 wip almost
2024-05-20 ender wip fast
2024-05-20 main program serial cmd ready
2024-05-21 wifi no timeout
2024-05-21 updete for test timeout
2024-05-22 bt wip
2024-05-22 wip bt
2024-05-22 wip fail
2024-05-22 correction state reset encoder
2024-05-22 BT config ready
2024-05-28 tester wip
2024-05-29 wip lib
2024-05-29 wip less flash
2024-05-29 working
2024-05-30 energy save wip
2024-06-12 keypad
2024-06-13 teclado wip
2024-06-14 encoder flow not change to false
2024-06-19 esp32 encoder
2024-06-19 sd card not list all files
2024-06-20 SIGFOX READY
2024-06-21 wip encoder
2024-06-21 ender wip, mqtt ready
2024-06-22 encoder delta
2024-06-22 wip star and stop encoder
2024-06-22 encoder flow and stop
2024-06-25 printer
2024-06-26 rtos wip, keyboard
2024-06-26 encoder and display keyboard ready
    wip on keyboard
2024-07-01 rele and valve ok
2024-07-01 wip vera
2024-07-03 wip base registro
2024-07-03 wip veracruz
2024-07-03 estable, wip on wifi semaphore, error
2024-07-04 wifi semaphore
2024-07-04 veracruz 1
2024-07-05 wip mongoose os
2024-07-05 sigfox no min_tesla
2024-07-05 Time Sleep and check
2024-07-07 lcd json wip
2024-07-08 wip jsondisp and encoder
2024-07-08 display ok
2024-07-08 best performance over clock 240
2024-07-08 display txt jsonrpc ok
    wip size and pos
2024-07-08 msg size pos ok
2024-07-08 SPECIAL FOR MEDIDOR
2024-07-09 display text ok, wip on img
2024-07-09 display ok, wip on service report
2024-07-10 sync cmd serial y serial1 ok
2024-07-16 wip on pc
2024-07-17 del mon
2024-07-18 start mos
2024-07-31 add pin for display master on enable pin
2024-07-31 new name for file
2024-08-04 wip display
2024-08-07 sigfox tester xyzA
